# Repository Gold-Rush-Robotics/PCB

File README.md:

# GRR PCBs
Repo for Custom PCB projects, Look at branches to find various projects, or Scroll down and click on a header

# [Main Board](https://github.com/Gold-Rush-Robotics/PCB/tree/main_board)

This is the main PCB for the GRR robot. This is where a bunch of stuff connects.
Preview Image:

# [Attachment Board](https://github.com/Gold-Rush-Robotics/PCB/tree/attachment_board)

This is a pcb made to attach to another PCB, for better connectivity to it.
Preview Image:

# [Drive Train Board](https://github.com/Gold-Rush-Robotics/PCB/tree/drivetrain_board)

This is a PCB made for the drive train. It attaches to 2 other PCBs, and is use to drive motors and stuff.
Preview Image:

👁️ Remeber, none of these board are real, becuase electricity isn't real. DON'T BELIEVE WHAT THEY TELL YOU!!!!! 👁️

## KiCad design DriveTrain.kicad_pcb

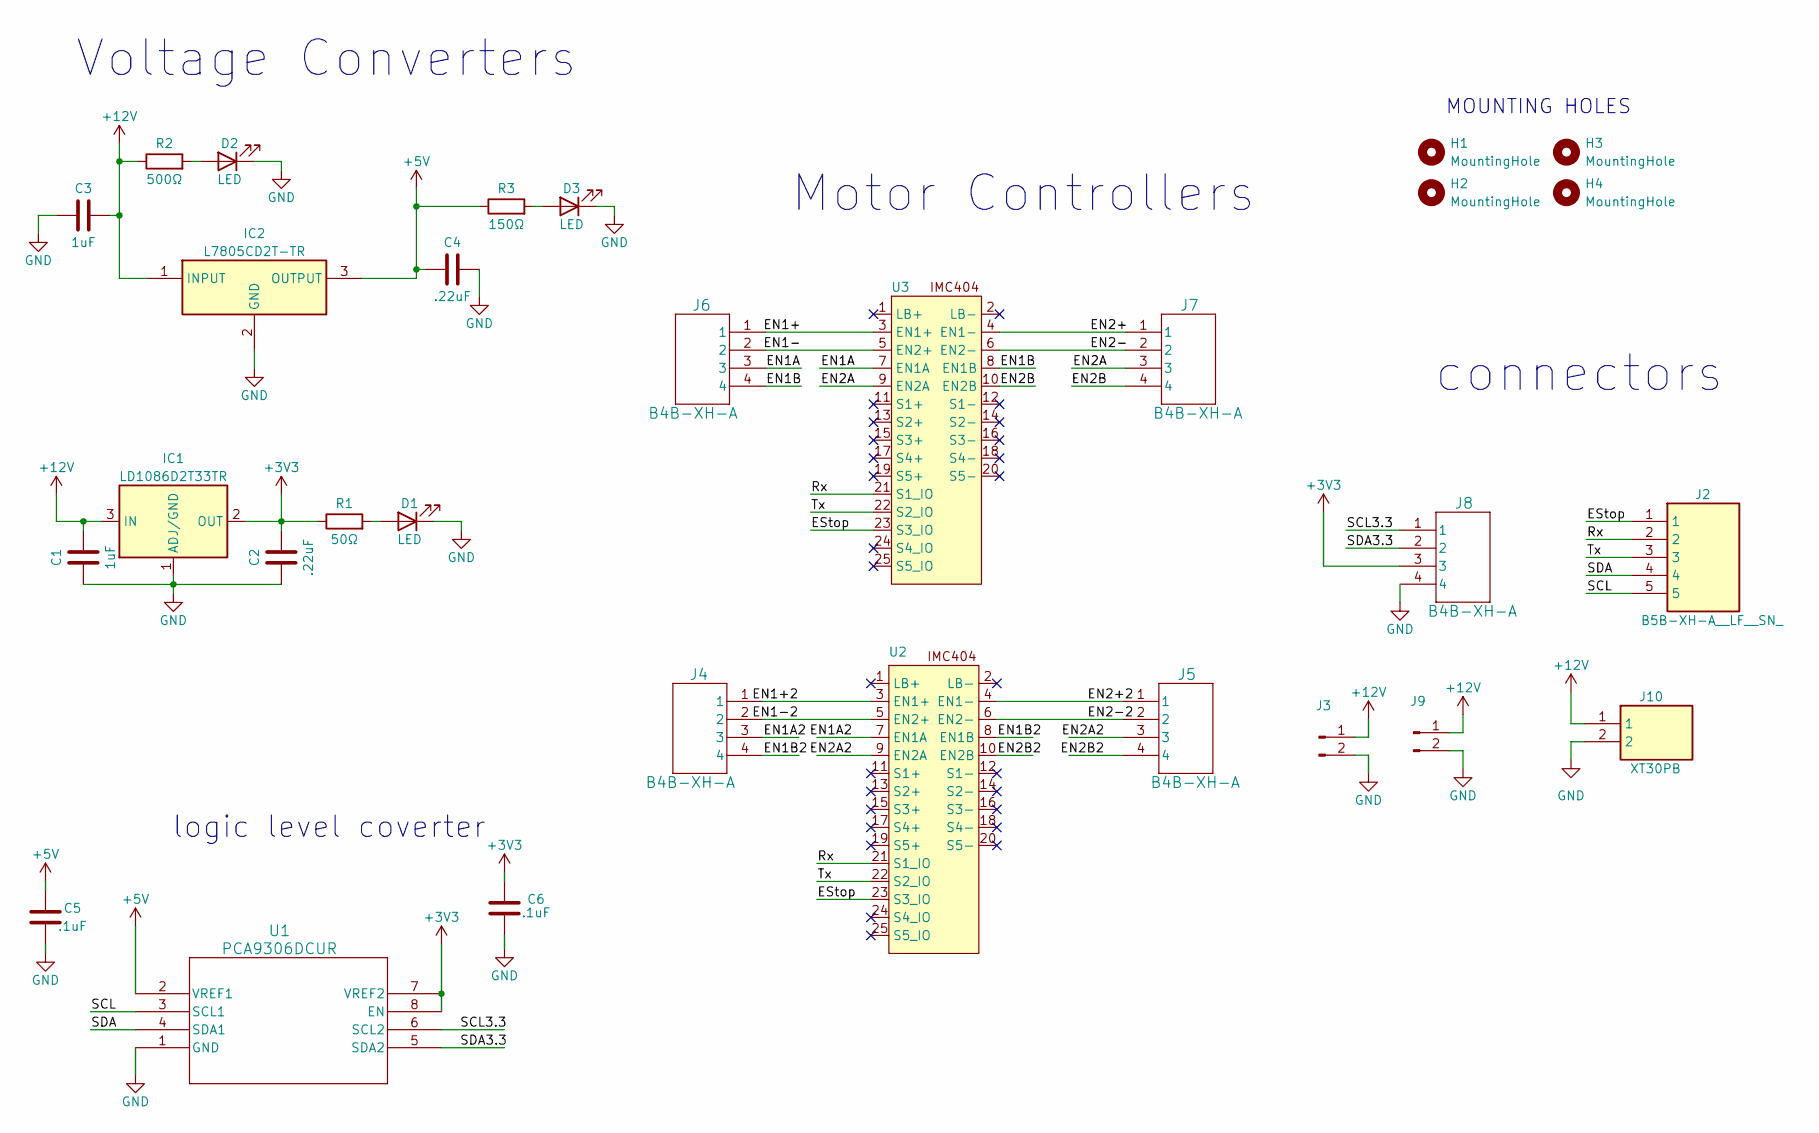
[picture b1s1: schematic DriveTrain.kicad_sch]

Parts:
C1, C3: 1uF; C_0603_1608Metric
C2, C4: .22uF; C_0603_1608Metric
C5, C6: .1uF; C_0603_1608Metric
D1: LED; D_0603_1608Metric
D2, D3: LED; LED_0603_1608Metric
H1, H2, H3, H4: MountingHole; MountingHole_3mm
IC1: LD1086D2T33TR; TO-263-2
IC2: L7805CD2T-TR; L7805CD2T; Manufacturer_Part_Number L7805CD2T-TR; Mouser Part Number 511-L7805CD2T-TR
J2: B5B-XH-A__LF__SN_; SHDR5W64P0X250_1X5_1490X575X700P; Manufacturer_Part_Number B5B-XH-A (LF)(SN)
J3, J9: Conn_01x02_Pin; 2mm_pads_4
J4, J5, J6, J7: B4B-XH-A; B4B-XH-A_JST
J8: B4B-XH-A; B4BXHA
J10: XT30PB; Manufacturer_Part_Number XT30PB
R1: 50Ω; R_0603_1608Metric
R2: 500Ω; R_0603_1608Metric
R3: 150Ω; R_0603_1608Metric
U1: PCA9306DCUR; SOP50P310X90-8N
U2, U3: IMC404

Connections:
+3V3: C2.2, C6.2, IC1.2 (OUT), J8.3, R1.1, U1.7 (VREF2), U1.8 (EN)
+5V: C4.2, C5.1, IC2.3 (OUTPUT), R3.1, U1.2 (VREF1)
+12V: C1.2, C3.2, IC1.3 (IN), IC2.1 (INPUT), J3.1, J9.1, J10.1, R2.1
/EN1+: J6.1, U3.3 (EN1+)
/EN1+2: J4.1, U2.3 (EN1+)
/EN1-: J6.2, U3.5 (EN2+)
/EN1-2: J4.2, U2.5 (EN2+)
/EN1A: J6.3, U3.7 (EN1A)
/EN1A2: J4.3, U2.7 (EN1A)
/EN1B: J6.4, U3.8 (EN1B)
/EN1B2: J4.4, U2.8 (EN1B)
/EN2+: J7.1, U3.4 (EN1-)
/EN2+2: J5.1, U2.4 (EN1-)
/EN2-: J7.2, U3.6 (EN2-)
/EN2-2: J5.2, U2.6 (EN2-)
/EN2A: J7.3, U3.9 (EN2A)
/EN2A2: J5.3, U2.9 (EN2A)
/EN2B: J7.4, U3.10 (EN2B)
/EN2B2: J5.4, U2.10 (EN2B)
/EStop: J2.1, U2.23 (S3_IO), U3.23 (S3_IO)
/Rx: J2.2, U2.21 (S1_IO), U3.21 (S1_IO)
/SCL: J2.5, U1.3 (SCL1)
/SCL3.3: J8.1, U1.6 (SCL2)
/SDA: J2.4, U1.4 (SDA1)
/SDA3.3: J8.2, U1.5 (SDA2)
/Tx: J2.3, U2.22 (S2_IO), U3.22 (S2_IO)
GND: C1.1, C2.1, C3.1, C4.1, C5.2, C6.1, D1.1 (K), D2.1 (K), D3.1 (K), IC1.1 (ADJ/GND), IC2.2 (GND), J3.2, J8.4, J9.2, J10.2, U1.1 (GND)
unnamed: D1.2 (A), R1.2
unnamed: D2.2 (A), R2.2
unnamed: D3.2 (A), R3.2

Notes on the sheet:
logic level coverter
Voltage Converters
MOUNTING HOLES
Motor Controllers
connectors

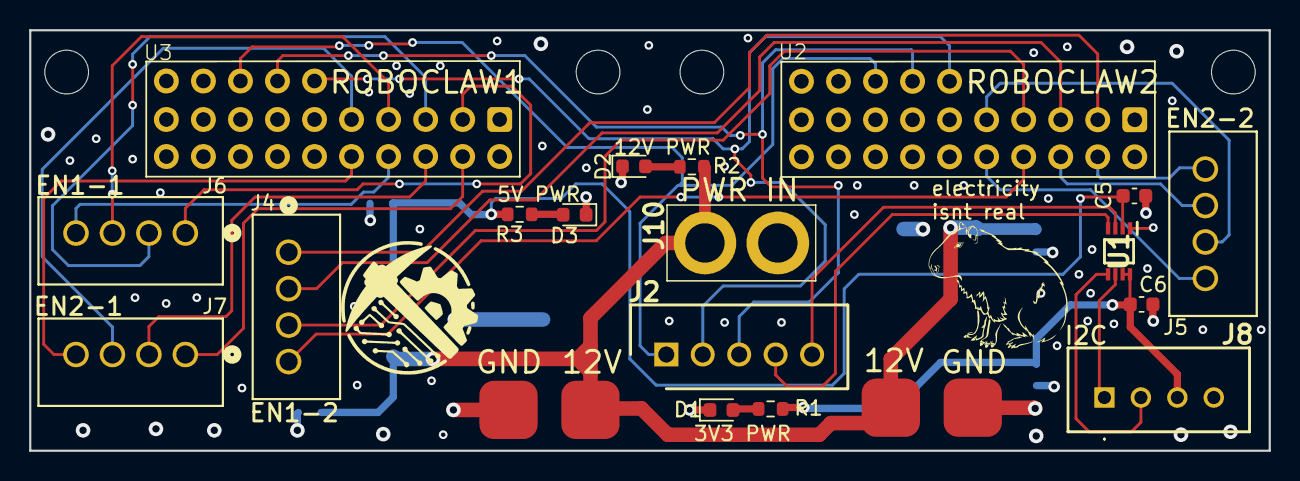
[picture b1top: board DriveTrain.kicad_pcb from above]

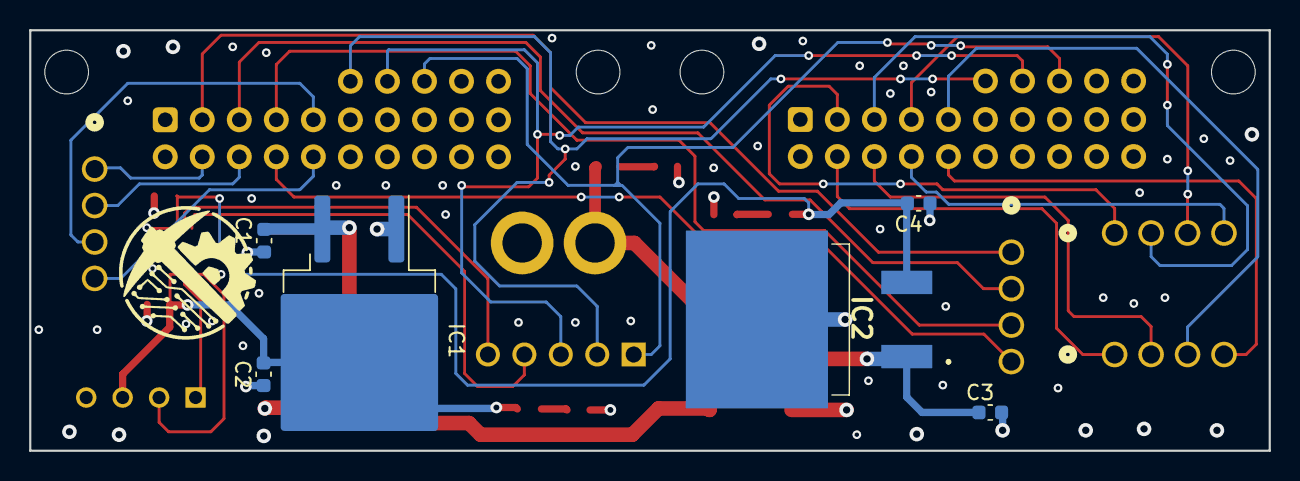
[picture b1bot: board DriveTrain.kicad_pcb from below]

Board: 4 copper layers, 85.0 x 28.8 mm, 30 parts (6 on the bottom side), 30 nets.

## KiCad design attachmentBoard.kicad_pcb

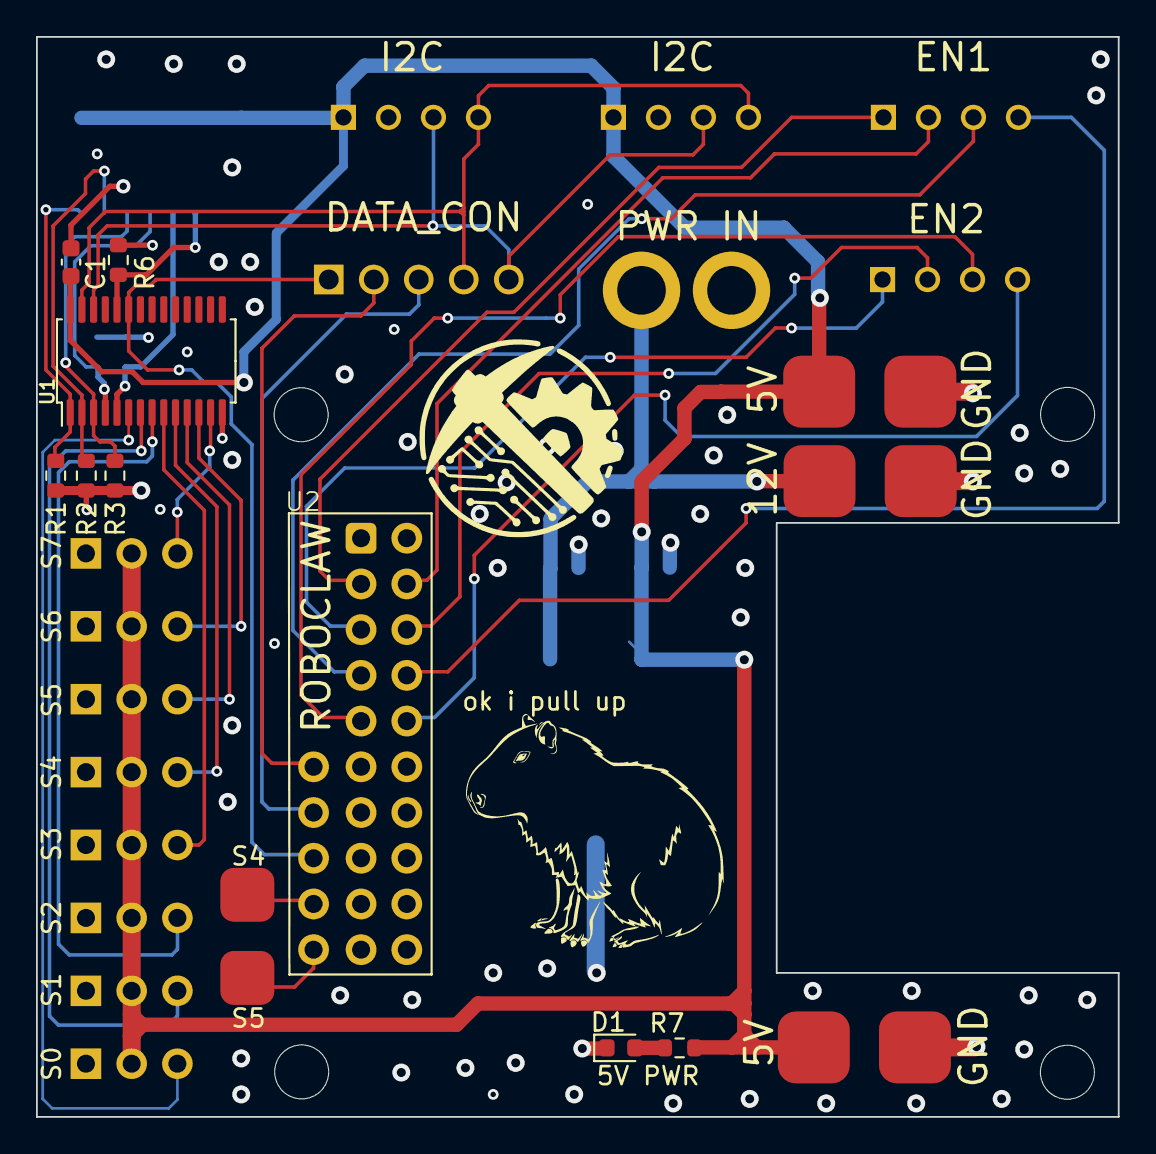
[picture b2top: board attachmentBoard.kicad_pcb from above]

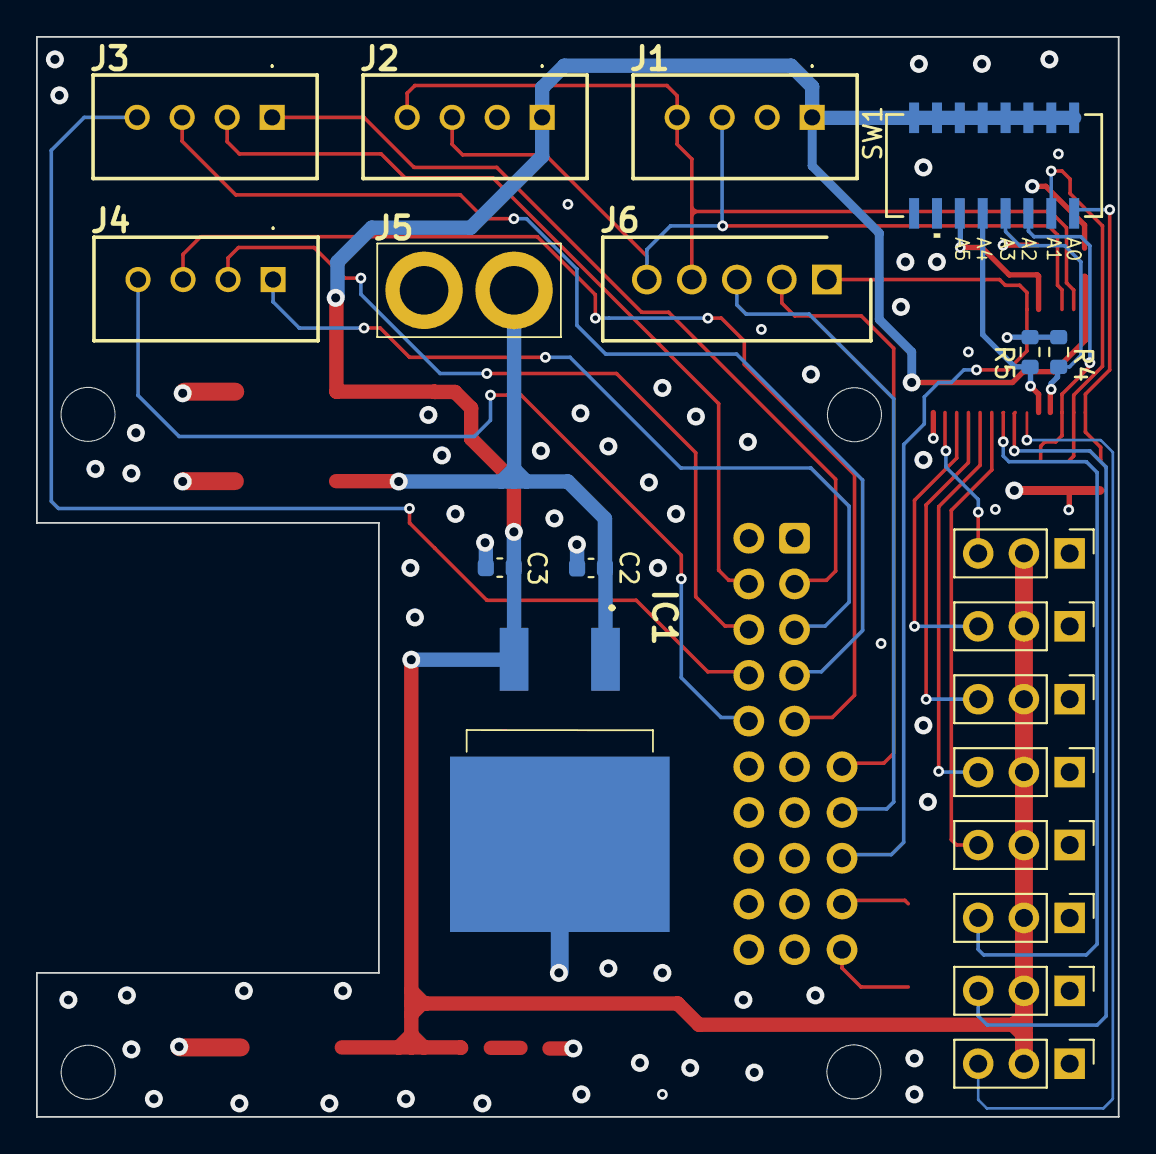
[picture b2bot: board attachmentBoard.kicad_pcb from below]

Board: 4 copper layers, 60.1 x 60.0 mm, 33 parts (20 on the bottom side), 33 nets.

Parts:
C1, C3: .1uF; C_0603_1608Metric
C2: .33uF; C_0603_1608Metric
D1: LED; LED_0603_1608Metric
IC1: L7805CD2T-TR; L7805CD2T
J1, J2, J3, J4: B4B-XH-A; B4BXHA
J5: XT30PB
J6: B5B-XH-A__LF__SN_; SHDR5W64P0X250_1X5_1490X575X700P
J7, J8, J9, J10: 4mm_pads_2
J11, J12, J13, J14, J15, J16, J17, J18: Conn_01x03; PinHeader_1x03_P2.54mm_Vertical
R1, R2, R3, R4, R5, R6: 1.02K; R_0603_1608Metric
R7: TBD; R_0603_1608Metric
SW1: CHS-08TA; CHS-08TA_NDC-M
U1: PCA9685PW; TSSOP-28_4.4x9.7mm_P0.65mm
U2: IMC404

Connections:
+5V: C1.1, C3.1, IC1.3 (OUTPUT), J1.1, J2.1, J8.1, J9.1, J11.2, J12.2, J13.2, J14.2, J15.2, J16.2, J17.2, J18.2, R7.1, SW1.1, SW1.2, SW1.3, SW1.4, SW1.5, SW1.6, SW1.7, SW1.8, U1.28 (VDD)
+12V: C2.1, IC1.1 (INPUT), J5.1, J7.1
/A0: R1.1, SW1.16, U1.1 (A0)
/A1: R2.1, SW1.15, U1.2 (A1)
/A2: R3.1, SW1.14, U1.3 (A2)
/A3: R4.1, SW1.13, U1.4 (A3)
/A4: R5.1, SW1.12, U1.5 (A4)
/A5: R6.1, SW1.11, U1.24 (A5)
/EN1+: J3.1, U2.3 (EN1+)
/EN1-: J3.2, U2.4 (EN1-)
/EN1A: J3.3, U2.7 (EN1A)
/EN1B: J3.4, U2.8 (EN1B)
/EN2+: J4.1, U2.5 (EN2+)
/EN2-: J4.2, U2.6 (EN2-)
/EN2A: J4.3, U2.9 (EN2A)
/EN2B: J4.4, U2.10 (EN2B)
/E_STOP: J6.1, U1.23 (~OE), U2.23 (S3_IO)
/RxD: J6.2, U2.21 (S1_IO)
/S4: J10.1, U2.24 (S4_IO)
/S5: J10.2, U2.25 (S5_IO)
/SCL: J1.3, J2.3, J6.5, U1.26 (SCL)
/SDA: J1.4, J2.4, J6.4, U1.27 (SDA)
/SERVO0: J11.3, U1.6 (LED0)
/SERVO1: J12.3, U1.7 (LED1)
/SERVO2: J13.3, U1.8 (LED2)
/SERVO3: J14.3, U1.9 (LED3)
/SERVO4: J15.3, U1.10 (LED4)
/SERVO5: J16.3, U1.11 (LED5)
/SERVO6: J17.3, U1.12 (LED6)
/SERVO7: J18.3, U1.13 (LED7)
/TxD: J6.3, U2.22 (S2_IO)
GND: C1.2, C2.2, C3.2, D1.1 (K), IC1.2 (GND), J1.2, J2.2, J5.2, J7.2, J8.2, J9.2, J11.1, J12.1, J13.1, J14.1, J15.1, J16.1, J17.1, J18.1, R1.2, R2.2, R3.2, R4.2, R5.2, R6.2, U1.14 (VSS)
unnamed: D1.2 (A), R7.2

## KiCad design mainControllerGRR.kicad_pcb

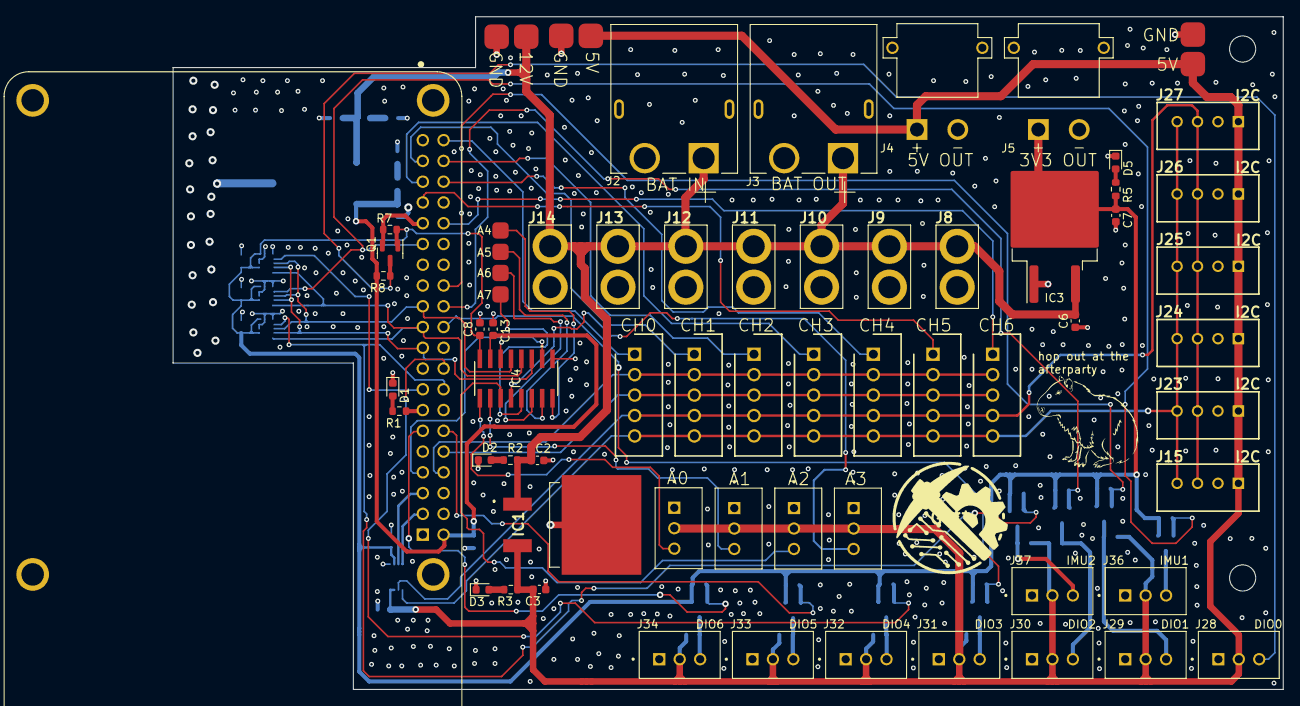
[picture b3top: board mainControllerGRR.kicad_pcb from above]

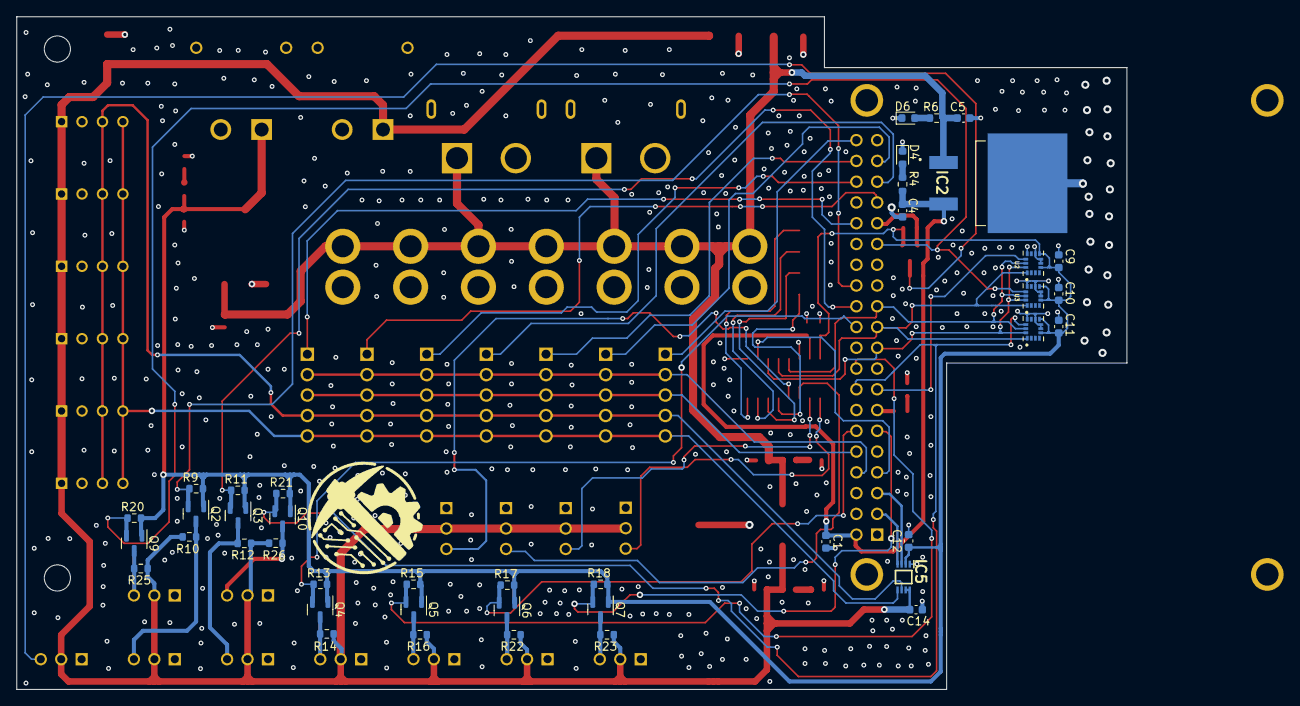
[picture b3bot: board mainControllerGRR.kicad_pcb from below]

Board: 4 copper layers, 135.8 x 82.3 mm, 105 parts (41 on the bottom side), 56 nets.

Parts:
C1, C8, C9, C10, C11, C12, C13, C14: 100nF; C_0603_1608Metric
C2, C5: .33uF; C_0603_1608Metric
C3, C4, C6, C7: .1uF; C_0603_1608Metric
D1, D2, D3, D4, D5, D6: LED; LED_0603_1608Metric
H2, H3: MountingHole; MountingHole_3.2mm_M3
IC1, IC2: L7805CD2T-TR; L7805CD2T
IC3: LD1086D2T33TR; TO-263-2
IC4: MCP3008-I_SL; SOIC16-N_MC_MCH-M
IC5: PCA9306DCUR; SOP50P310X90-8N
J1: Raspberry_Pi_2_3; MODULE_RASPBERRY_PI_3_MODEL_B_
J2, J3: XT60PW-M; AMASS_XT60PW-M
J4, J5: XT30PW-M; AMASS_XT30PW-M
J6, J42: Conn_01x02; 4mm_pads_2
J7: Conn_01x04; 4mm_pads_2_1
J8, J9, J10, J11, J12, J13, J14: XT30PB
J15, J23, J24, J25, J26, J27: B4B-XH-A; B4BXHA
J16, J17, J18, J19, J20, J21, J22: B5B-XH-A__LF__SN_; SHDR5W64P0X250_1X5_1490X575X700P
J28, J29, J30, J31, J32, J33, J34, J36, J37, J38, J39, J40, J41: B3B-XH-A_LF__SN_; JST_B3B-XH-A_LF__SN_
Je1: Conn_01x02; 4mm_pads_2
Q1, Q2, Q3, Q4, Q5, Q6, Q7, Q9, Q10: BSS138; SOT-23
R1: 1.5 Ω; R_0603_1608Metric
R2, R5, R6: 44Ω; R_0603_1608Metric
R3: IDK; R_0603_1608Metric
R4: idk; R_0603_1608Metric
R7, R8, R9, R10, R11, R12, R13, R14, R15, R16, R17, R18, R20, R21, R22, R23, R25, R26: 10K; R_0603_1608Metric
U2, U3, U4: ICM-42688-P; PQFN50P300X250X97-14N

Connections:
5V_BRAIN: C1.1, C4.2, C13.1, IC2.3 (OUTPUT), IC4.15 (VREF), J1.2 (5V), R4.1, R8.1
+3V3: C7.2, C8.1, C9.1, C10.1, C11.1, C12.1, IC3.2 (OUT), IC4.16 (VDD), IC5.2 (VREF1), J5.P, Q1.1 (G), Q2.1 (G), Q3.1 (G), Q4.1 (G), Q5.1 (G), Q6.1 (G), Q7.1 (G), Q9.1 (G), Q10.1 (G), R5.1, R7.1, R9.1, R11.1, R13.1, R15.1, R17.1, R18.1, R20.1, R21.1, U2.5 (VDDIO), U2.8 (VDD), U3.5 (VDDIO), U3.8 (VDD), U4.5 (VDDIO), U4.8 (VDD)
+5V: C3.2, C14.1, IC1.3 (OUTPUT), IC5.7 (VREF2), IC5.8 (EN), J4.P, J6.1, J15.1, J23.1, J24.1, J25.1, J26.1, J27.1, J28.2, J29.2, J30.2, J31.2, J32.2, J33.2, J34.2, J36.2, J37.2, J38.2, J39.2, J40.2, J41.2, J42.1, R3.1, R10.1, R12.1, R14.1, R16.1, R22.1, R23.1, R25.1, R26.1
+12V: C2.2, C5.2, C6.2, IC1.1 (INPUT), IC2.1 (INPUT), IC3.3 (IN), J2.1 (+), J3.1 (+), J8.1, J9.1, J10.1, J11.1, J12.1, J13.1, J14.1, Je1.1, R2.1, R6.1
A0EStop: J1.40 (GPIO21/SCLK1), J16.1
A1EStop: J1.37 (GPIO26), J17.1
A2EStop: J1.38 (GPIO20/MOSI1), J18.1
A3EStop: J1.35 (GPIO19/MISO1), J19.1
A4EStop: J1.36 (GPIO16), J20.1
A5EStop: J1.33 (PWM1/GPIO13), J21.1
A6EStop: J1.32 (PWM0/GPIO12), J22.1
ADC: IC4.10 (~CS/SHDN), J1.7 (GCLK0/GPIO4)
DIO0: J1.31 (GCLK2/GPIO6), Q1.2 (S), R7.2
DIO0_5V: J28.3, Q1.3 (D), R8.2
DIO1: J1.26 (~CE1/GPIO7), Q2.2 (S), R9.2
DIO1_5V: J29.3, Q2.3 (D), R10.2
DIO2: J1.24 (~CE0/GPIO8), Q3.2 (S), R11.2
DIO2_5V: J30.3, Q3.3 (D), R12.2
DIO3: J1.22 (GPIO25), Q4.2 (S), R13.2
DIO3_5V: J31.3, Q4.3 (D), R14.2
DIO4: J1.18 (GPIO24), Q5.2 (S), R15.2
DIO4_5V: J32.3, Q5.3 (D), R16.2
DIO5: J1.12 (GPIO18/PWM0), Q6.2 (S), R17.2
DIO5_5V: J33.3, Q6.3 (D), R22.2
DIO6: J1.11 (GPIO17), Q7.2 (S), R18.2
DIO6_5V: J34.3, Q7.3 (D), R23.2
GND: C1.2, C2.1, C3.1, C4.1, C5.1, C6.1, C7.1, C8.2, C9.2, C10.2, C11.2, C12.2, C13.2, C14.2, D1.1 (K), D2.1 (K), D3.1 (K), D4.1 (K), D5.1 (K), D6.1 (K), IC1.2 (GND), IC2.2 (GND), IC3.1 (ADJ/GND), IC4.9 (DGND), IC4.14 (AGND), IC5.1 (GND), J1.6 (GND), J1.9 (GND), J1.14 (GND), J1.20 (GND), J1.25 (GND), J1.30 (GND), J1.34 (GND), J1.39 (GND), J2.2 (-), J3.2 (-), J4.N, J5.N, J6.2, J8.2, J9.2, J10.2, J11.2, J12.2, J13.2, J14.2, J15.2, J23.2, J24.2, J25.2, J26.2, J27.2, J28.1, J29.1, J30.1, J31.1, J32.1, J33.1, J34.1, J36.1, J37.1, J38.1, J39.1, J40.1, J41.1, J42.2, Je1.2, U2.6 (GND), U2.7 (RESV_7), U2.9 (INT2/FSYNC/CLKIN), U2.11 (RESV_11), U3.6 (GND), U3.7 (RESV_7), U3.9 (INT2/FSYNC/CLKIN), U3.11 (RESV_11), U4.6 (GND), U4.7 (RESV_7), U4.9 (INT2/FSYNC/CLKIN), U4.11 (RESV_11)
IMU0: J1.15 (GPIO22), U2.12 (AP_CS)
IMU1: J1.29 (GCLK1/GPIO5), Q9.2 (S), R20.2, U3.12 (AP_CS)
IMU1_5V: J36.3, Q9.3 (D), R25.2
IMU2: J1.16 (GPIO23), Q10.2 (S), R21.2, U4.12 (AP_CS)
IMU2_5V: J37.3, Q10.3 (D), R26.2
MISO: IC4.12 (DOUT), J1.21 (MISO0/GPIO9), U2.1 (AP_SDO/AP_AD0), U3.1 (AP_SDO/AP_AD0), U4.1 (AP_SDO/AP_AD0)
MOSI: IC4.11 (DIN), J1.19 (MOSI0/GPIO10), U2.14 (AP_SDA/AP_SDIO/AP_SDI), U3.14 (AP_SDA/AP_SDIO/AP_SDI), U4.14 (AP_SDA/AP_SDIO/AP_SDI)
unnamed: D1.2 (A), R1.1
unnamed: D2.2 (A), R2.2
unnamed: D3.2 (A), R3.2
unnamed: D4.2 (A), R4.2
unnamed: D5.2 (A), R5.2
unnamed: D6.2 (A), R6.2
unnamed: IC4.1 (CH0), J38.3
unnamed: IC4.2 (CH1), J39.3
unnamed: IC4.3 (CH2), J40.3
unnamed: IC4.4 (CH3), J41.3
unnamed: IC4.5 (CH4), J7.4
unnamed: IC4.6 (CH5), J7.3
unnamed: IC4.7 (CH6), J7.2
unnamed: IC4.8 (CH7), J7.1
unnamed: J1.13 (GPIO27), R1.2
RxD: J1.8 (GPIO14/TXD), J16.2, J17.2, J18.2, J19.2, J20.2, J21.2, J22.2
SCK: IC4.13 (CLK), J1.23 (SCLK0/GPIO11), U2.13 (AP_SCL/AP_SCLK), U3.13 (AP_SCL/AP_SCLK), U4.13 (AP_SCL/AP_SCLK)
SCL: IC5.6 (SCL2), J15.3, J16.4, J17.4, J18.4, J19.4, J20.4, J21.4, J22.4, J23.3, J24.3, J25.3, J26.3, J27.3
SCL_3.3V: IC5.3 (SCL1), J1.5 (SCL/GPIO3)
SDA: IC5.5 (SDA2), J15.4, J16.5, J17.5, J18.5, J19.5, J20.5, J21.5, J22.5, J23.4, J24.4, J25.4, J26.4, J27.4
SDA_3.3V: IC5.4 (SDA1), J1.3 (SDA/GPIO2)
TxD: J1.10 (GPIO15/RXD), J16.3, J17.3, J18.3, J19.3, J20.3, J21.3, J22.3

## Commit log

2023-11-07 migrating from personal repo https://github.com/SonOfCheevap/GRRMainBoard
2023-11-07 migrating from personal repo
2023-11-07 moving from personal repo
2023-11-08 Added gerber files
2023-11-10 working on adding JLC part numbers
2023-11-10 add a gitignore for autosave files
2023-11-14 Changed capacitor values on 12v convertor
2023-11-28 add schematic pdf
2023-11-28 drivetrain board schematic
